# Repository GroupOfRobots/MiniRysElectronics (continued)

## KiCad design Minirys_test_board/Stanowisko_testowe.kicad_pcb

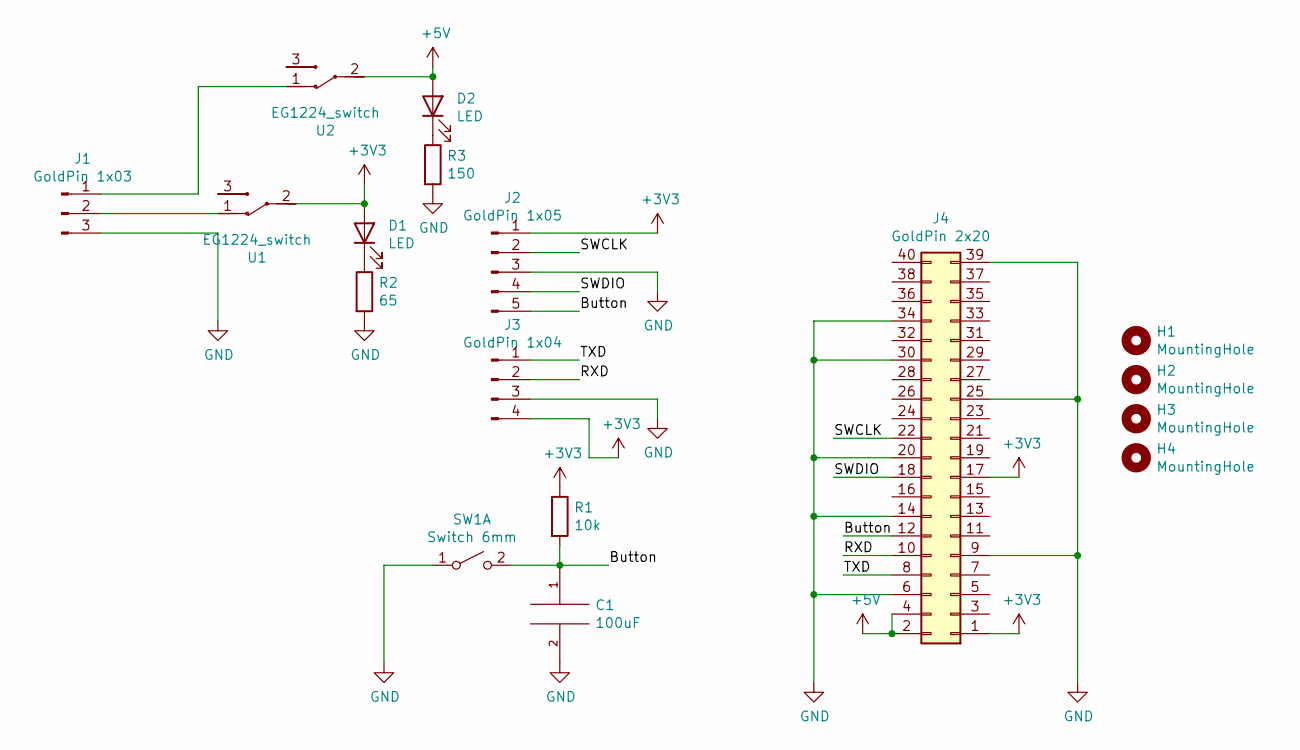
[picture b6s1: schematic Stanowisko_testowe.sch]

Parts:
C1: 100uF; C_0603_1608Metric_Pad1.08x0.95mm_HandSolder
D1, D2: LED; LED_0603_1608Metric
H1, H2, H3, H4: MountingHole; MountingHole_2.7mm_M2.5_Pad
J1: GoldPin 1x03; PinHeader_1x03_P2.54mm_Vertical
J2: GoldPin 1x05; PinHeader_1x05_P2.54mm_Vertical
J3: GoldPin 1x04; PinHeader_1x04_P2.54mm_Vertical
J4: GoldPin 2x20; PinHeader_2x20_P2.54mm_Vertical
R1: 10k; R_0603_1608Metric_Pad0.98x0.95mm_HandSolder
R2: 65; R_0603_1608Metric_Pad0.98x0.95mm_HandSolder
R3: 150; R_0603_1608Metric_Pad0.98x0.95mm_HandSolder
SW1: Switch 6mm; SW_PUSH_6mm
U1, U2: EG1224_switch; SW_E-Switch_EG1224_SPDT_Angled

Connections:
+3V3: D1.2 (A), J2.1, J3.4, J4.1, J4.17, R1.1, U1.2
+5V: D2.2 (A), J4.2, J4.4, U2.2
/Button: C1.1, J2.5, J4.12, R1.2, SW1.2 (B)
/RXD: J3.2, J4.10
/SWCLK: J2.2, J4.22
/SWDIO: J2.4, J4.18
/TXD: J3.1, J4.8
GND: C1.2, J1.3, J2.3, J3.3, J4.6, J4.9, J4.14, J4.20, J4.25, J4.30, J4.34, J4.39, R2.2, R3.2, SW1.1 (A)
unnamed: D1.1 (K), R2.1
unnamed: D2.1 (K), R3.1
unnamed: J1.1, U2.1
unnamed: J1.2, U1.1

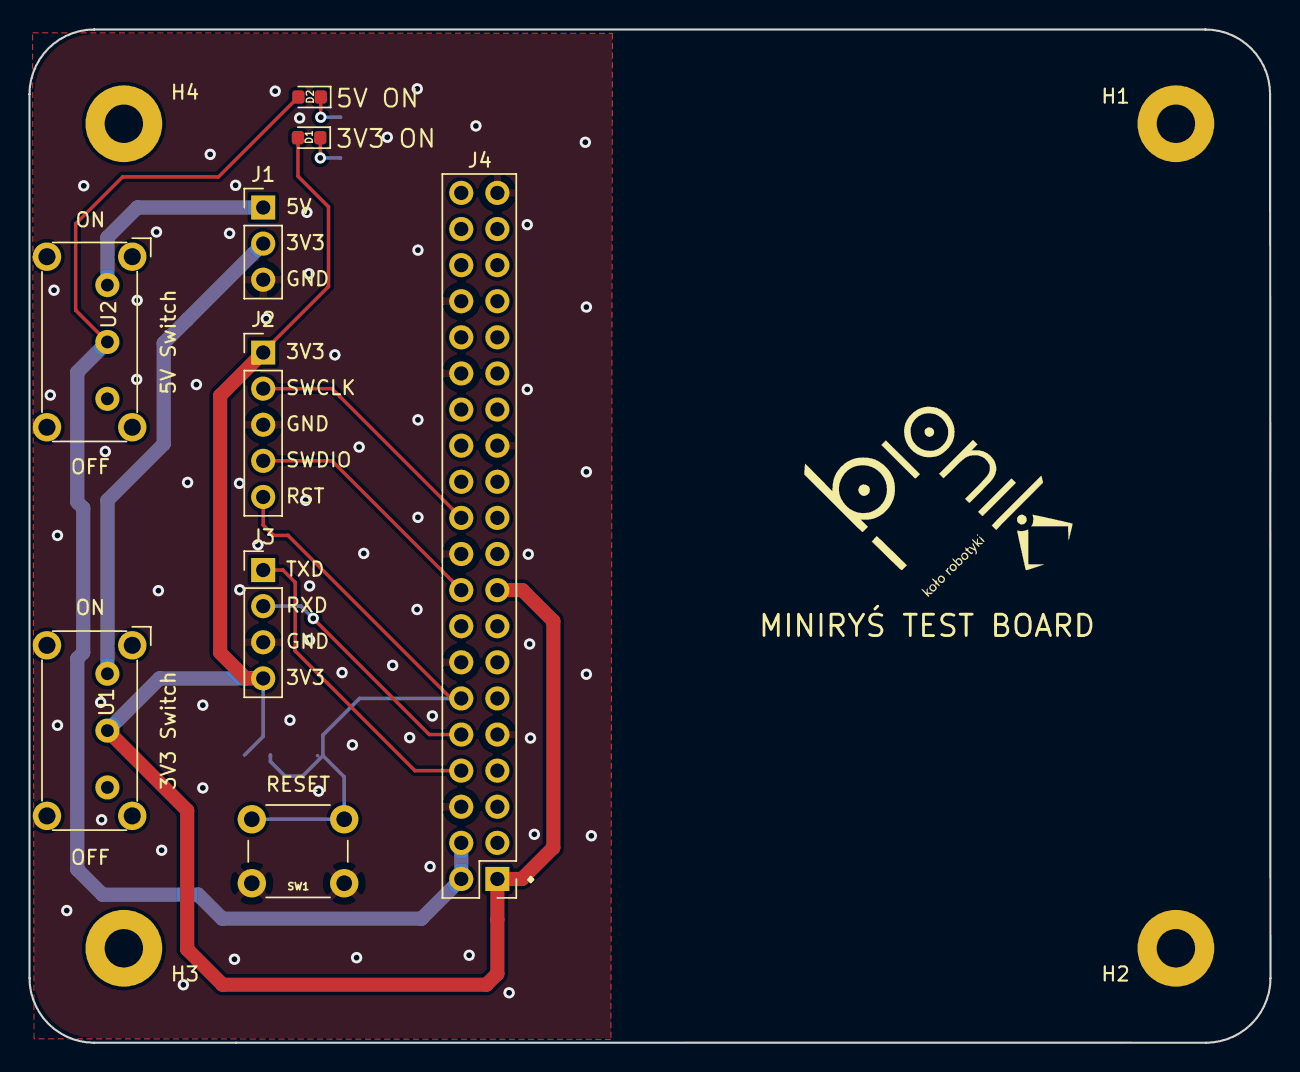
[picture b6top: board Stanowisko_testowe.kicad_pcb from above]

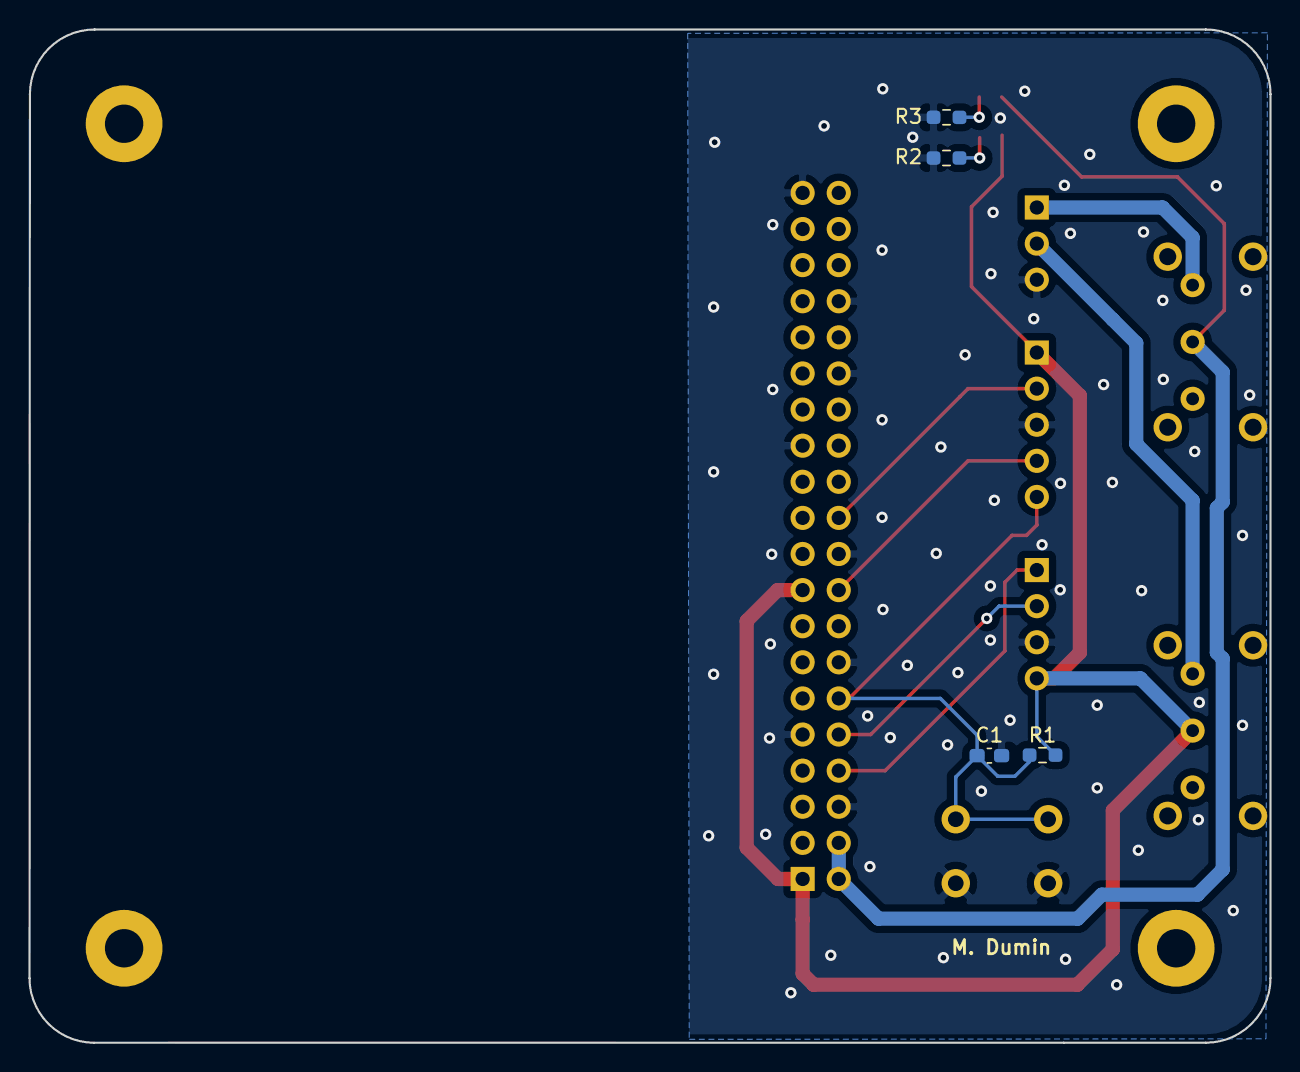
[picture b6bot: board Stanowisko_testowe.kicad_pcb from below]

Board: 2 copper layers, 87.3 x 71.3 mm, 18 parts (4 on the bottom side), 12 nets.

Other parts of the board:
LOGO1: bionik_logo

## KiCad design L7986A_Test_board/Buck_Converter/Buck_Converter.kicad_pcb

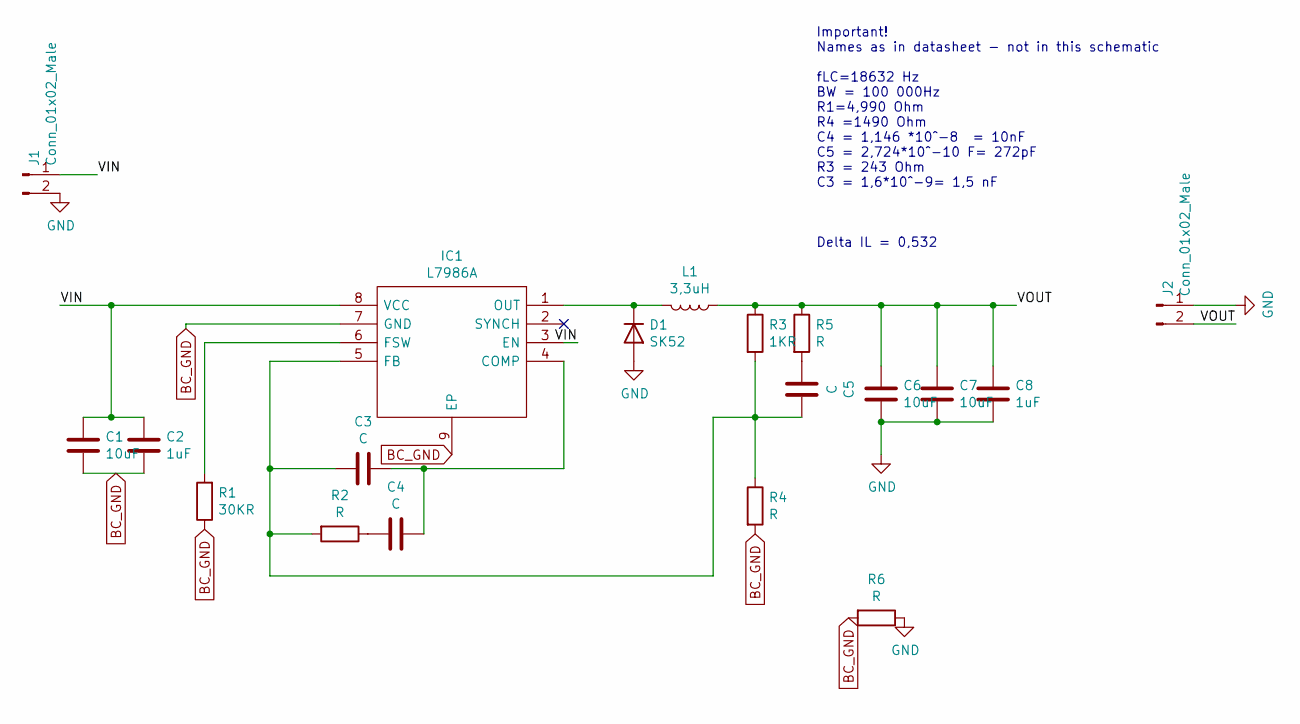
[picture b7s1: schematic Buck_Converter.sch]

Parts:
C1, C6, C7: 10uF; C_1206_3216Metric
C2: 1uF; C_0603_1608Metric
C3, C4, C5: C; C_0603_1608Metric
C8: 1uF; C_1206_3216Metric
D1: SK52; D_SMB
IC1: L7986A; SOIC127P600X170-9N; Mouser Part Number 511-L7986A
J1, J2: Conn_01x02_Male; PinHeader_1x02_P2.54mm_Vertical
L1: 3,3uH; L_6.3x6.3_H3
R1: 30KR; R_0603_1608Metric
R2, R4, R5, R6: R; R_0603_1608Metric
R3: 1KR; R_0603_1608Metric

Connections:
/VIN: C1.2, C2.2, IC1.3 (EN), IC1.8 (VCC), J1.1
/VOUT: C6.2, C7.2, C8.2, J2.2, L1.1, R3.1, R5.1
BC_GND: C1.1, C2.1, IC1.7 (GND), IC1.9 (EP), R1.1, R4.2, R6.2
GND: C6.1, C7.1, C8.1, D1.2 (A), J1.2, J2.1, R6.1
unnamed: C3.1, C4.1, IC1.4 (COMP)
unnamed: C3.2, C5.1, IC1.5 (FB), R2.2, R3.2, R4.1
unnamed: C4.2, R2.1
unnamed: C5.2, R5.2
unnamed: D1.1 (K), IC1.1 (OUT), L1.2
unnamed: IC1.6 (FSW), R1.2

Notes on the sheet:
Important! Names as in datasheet - not in this schematic fLC=18632 Hz BW = 100 000Hz R1=4,990 Ohm R4 =1490 Ohm C4 = 1,146 *10^-8 = 10nF C5 = 2,724*10^-10 F= 272pF R3 = 243 Ohm C3 = 1,6*10^-9= 1,5 nF Delta IL = 0,532

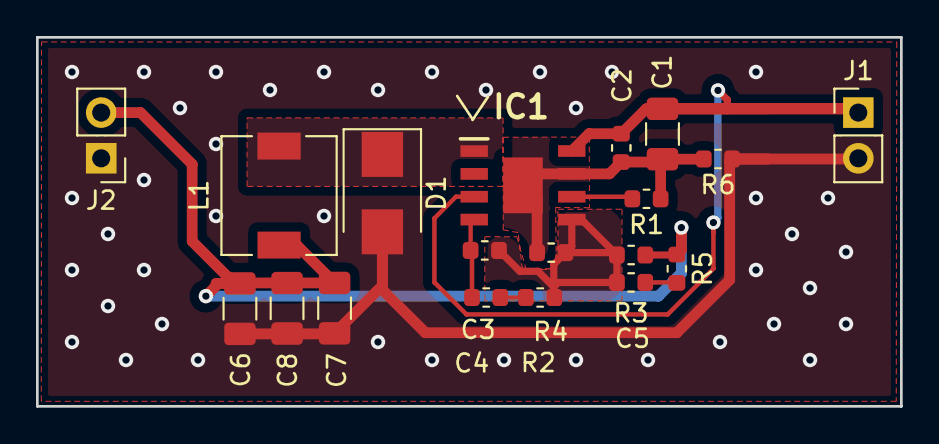
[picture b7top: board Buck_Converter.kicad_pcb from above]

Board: 2 copper layers, 48.0 x 20.5 mm, 19 parts (0 on the bottom side), 10 nets.

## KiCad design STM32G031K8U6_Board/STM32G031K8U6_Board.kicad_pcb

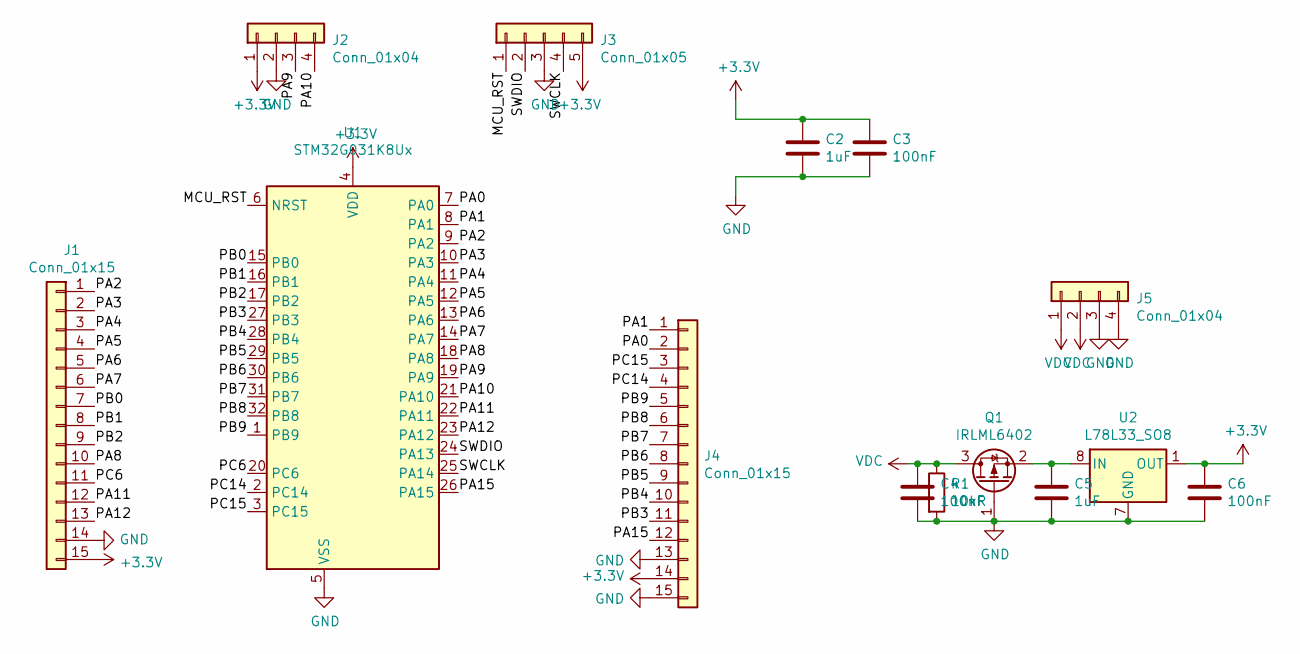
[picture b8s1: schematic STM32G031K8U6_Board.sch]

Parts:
C2, C5: 1uF; C_1206_3216Metric_Pad1.42x1.75mm_HandSolder
C3, C4, C6: 100nF; C_1206_3216Metric_Pad1.42x1.75mm_HandSolder
J1, J4: Conn_01x15; PinHeader_1x15_P2.54mm_Vertical
J2, J5: Conn_01x04; PinHeader_1x04_P2.54mm_Vertical
J3: Conn_01x05; PinHeader_1x05_P2.54mm_Vertical
Q1: IRLML6402; SOT-23
R1: 10kR; R_1206_3216Metric_Pad1.42x1.75mm_HandSolder
U1: STM32G031K8Ux; QFN-32-1EP_5x5mm_P0.5mm_EP3.45x3.45mm
U2: L78L33_SO8; SOIC-8_3.9x4.9mm_P1.27mm

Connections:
+3V3: C2.1, C3.1, C6.1, J1.15, J2.1, J3.5, J4.14, U1.4 (VDD), U2.1 (OUT)
/MCU_RST: J3.1, U1.6 (NRST)
/PA0: J4.2, U1.7 (PA0)
/PA1: J4.1, U1.8 (PA1)
/PA2: J1.1, U1.9 (PA2)
/PA3: J1.2, U1.10 (PA3)
/PA4: J1.3, U1.11 (PA4)
/PA5: J1.4, U1.12 (PA5)
/PA6: J1.5, U1.13 (PA6)
/PA7: J1.6, U1.14 (PA7)
/PA8: J1.10, U1.18 (PA8)
/PA9: J2.3, U1.19 (PA9)
/PA10: J2.4, U1.21 (PA10)
/PA11: J1.12, U1.22 (PA11)
/PA12: J1.13, U1.23 (PA12)
/PA15: J4.12, U1.26 (PA15)
/PB0: J1.7, U1.15 (PB0)
/PB1: J1.8, U1.16 (PB1)
/PB2: J1.9, U1.17 (PB2)
/PB3: J4.11, U1.27 (PB3)
/PB4: J4.10, U1.28 (PB4)
/PB5: J4.9, U1.29 (PB5)
/PB6: J4.8, U1.30 (PB6)
/PB7: J4.7, U1.31 (PB7)
/PB8: J4.6, U1.32 (PB8)
/PB9: J4.5, U1.1 (PB9)
/PC6: J1.11, U1.20 (PC6)
/PC14: J4.4, U1.2 (PC14)
/PC15: J4.3, U1.3 (PC15)
/SWCLK: J3.4, U1.25 (PA14)
/SWDIO: J3.2, U1.24 (PA13)
GND: C2.2, C3.2, C4.2, C5.2, C6.2, J1.14, J2.2, J3.3, J4.13, J4.15, J5.3, J5.4, Q1.1 (G), R1.2, U1.5 (VSS), U2.2 (GND), U2.3 (GND), U2.6 (GND), U2.7 (GND)
unnamed: C5.1, Q1.2 (S), U2.8 (IN)
VDC: C4.1, J5.1, J5.2, Q1.3 (D), R1.1

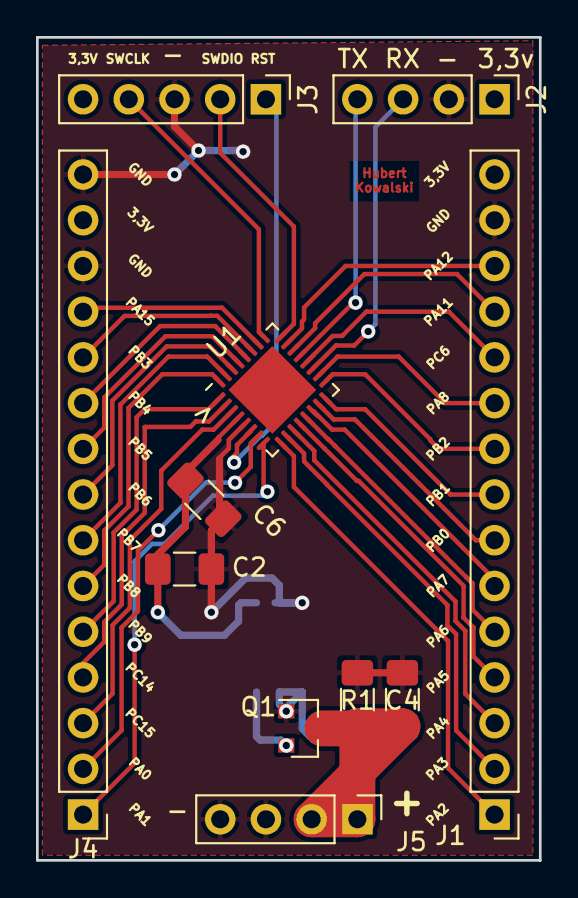
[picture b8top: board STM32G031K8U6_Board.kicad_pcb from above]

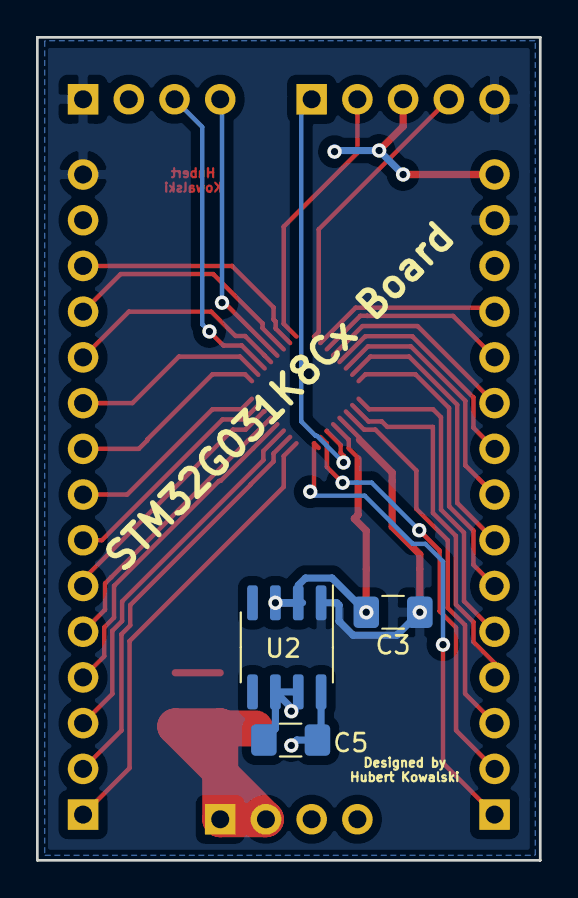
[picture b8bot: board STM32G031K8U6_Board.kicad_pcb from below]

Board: 2 copper layers, 27.9 x 45.7 mm, 14 parts (3 on the bottom side), 34 nets.

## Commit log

2016-03-23 initial
2016-03-28 nie chce misie
2016-03-31 initial board elements
2016-04-01 pcb updated
2016-04-01 allsmd
2016-04-05 allparts
2016-04-07 boardf
2016-04-07 clean
2016-05-11 useful mods
2016-06-19 starting new version
2016-06-19 beagleoutline
2016-06-21 powerconn
2016-06-25 powerconectors
2016-07-17 beaglepinout
2016-07-18 bgsignals
2016-07-18 schematiccomplete
2016-08-21 main wires
2016-08-24 boardv2 ready to check
2016-08-30 check pinout
2016-09-13 added distance sensor connectors
2016-09-26 gerbers
2016-10-09 gpioadjustment
2016-10-17 removes
2016-10-28 check and reconfigure gpios
2016-11-01 pin recinfiguration started
2016-11-06 new gpio routed started
2016-11-07 before logo
2016-11-07 v3gerbers
2016-11-13 pullups
2016-11-25 values
2016-12-11 right sonar wires
2017-01-26 new ideas
2017-04-06 v3init
2017-04-11 sdsd
2017-04-27 v3-ready
2017-04-30 ojojoj
2017-04-30 report
2017-05-05 gerbery
2017-05-06 wysłane
2017-06-16 TOF GPIO, pulldowns
2017-06-17 board 3.1: * zmienione szyny I2C1->I2C2, SPI1->SPI0 * poprawione dzielniki napięcia baterii * dodany dzielnik napięcia czujnika temperatury * poprawione etykiety i rozmieszczenie elementów na schemac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
2017-06-20 board v3.1 beta 5: przepięte 2 TOF i MEN,M0,M1,M2, usunięte rezystory z tych linii, rerouting
2017-06-21 gerber files, board report
2017-06-21 packed gerbers
2017-06-21 board v3.1 beta 6: poprawione dzielniki napięcia baterii na płytce
2017-06-23 board v3.1 beta 6: poprawiony minimalny rozmiar otworu (DRC)
2017-06-28 dwm1000_addon: mini-płytka na moduł dwm1000 wpinana na złącze goldpin
2017-07-07 dwm1000_addon: poprawione prowadzenie ścieżek masy
2017-07-07 board v3.1 beta 6: poprawione acid-trap przy dzielnikach napięcia baterii
2017-07-07 board v3.1 beta 7: replaced DWM1000 module with connector for dwm1000-addon board, redone battery cell voltage routes. No more vias.
2017-07-07 board v3.1 beta 7: fixed bad networks between motor drivers and connectors; fixed some clearance issues
2017-07-07 beacon: import płytki latarni lokalizacyjnej z repo RobotLocalization; rev 1.1: dwm1000 zastąpiony złączem na dwm1000-addon
2017-07-20 dwm1000_addon: zmniejszone pole masy pod anteną, przesunięte diody aktywności
2017-07-31 gitignore: gerbery dodane do ignorowanych
2017-07-31 latarnia (beacon): zmniejszone wymiary płytki
2017-07-31 dwm1000 addon: dodane pola masy
2017-08-01 dodane wymiary zewnętrzne płytek
2017-08-01 dodane archiwa z przygotowanymi gerberami aktualnych wersji płytek
2017-12-13 board3.1: updated resistors on voltage divider for power
2018-03-03 v4 init
2018-07-19 battery pcb model
2018-08-07 pico blade connectors
2018-10-17 raspberry layout
2018-10-18 power button
2018-10-21 battery module
2018-10-25 new battery module
2018-10-25 revision
2018-11-28 v4.1 schematic
2018-11-29 board adjustments on PCB
2018-12-04 v4.1
2018-12-27 regulator devider
2019-03-02 clean up repo and add TODO task
2019-03-02 improved battery module pads
2019-03-17 voltage devider fix
2019-04-13 ADC voltage divider
2019-05-18 v 4.1
2019-06-08 closed version 4.1
2019-08-05 new pads
2020-03-22 remove old versions (existing in git history)
2020-03-29 rysboard: converted to kicad (initial version)
2020-03-29 rysboard: rpi4 connector and power supply cleaned up after import; clean up library and gitignore file
2020-03-29 rysboard: schematic cleanup done after kicad import
2020-03-29 rysboard: library cleanup, fix bad connector references
2020-04-19 rysboard: 4.2 schematic
    Change the I2C buses and GPIOs used
    Fix L6470 connections
    Change ADC to 4-channel
    Add 2 user LEDs
    Add I2C pullups
    Add serial connector
2020-04-19 rysboard: 4.2 schematic imported to pcb, initial version
2020-05-16 rysboard 4.2: * add converter output protection (shottky, D8) * fix converter resistor values (R13/R14) * add 5Vgood LED (D9) * add PWR_FLAGs for KiCAD's ERC * add NAND for motor driver's output flag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
2020-05-16 rysboard v4.2: * route the whole board (TODO: ground fills, track width checks) * fix half of ToF connectors missing ground connection * swap LEDs for easier routing
2020-05-16 rysboard v4.2: adjust placement of text on pcb front side silkscreen
2020-05-17 rysboard v4.2: * re-add mountting holes * fix some layout errors * add ground fills * ensure proper track width * add front-side filkscreen
2020-05-17 rysboard v4.2: adjust silkscreen text positions, add board name, minor layout improvements
2020-05-19 rysboard v4.2: custom 6.7x6.7mm inductor footprint&model
2020-05-19 rysboard v4.2: status LED transistor swapped for BC847BS; PCB design fixes after review (!1)
2020-05-20 rysboard: remove additional i2c pullups; increase high-voltage track clearance
2020-05-24 rysboard: changed LED and sensors' VCC to 5V
2020-05-26 rysboard: move spi external interrupt line further from the edge
2020-06-24 rysboard: fix pour between SMD pins, fix acid pits, add +/- labels to battery connectors and Vdrive test point/area
2020-06-27 rysboard: fix additional acid pits, C15 cap placement, text orientation, added BIONIK logo and external SPI connector pinout
2020-06-27 rysboard: add missing molex 3d models
2020-08-23 rysboard: add PWM fan output
2020-10-23 rysboard: move the camera ribbon slot closer to the port on the Pi
2020-10-23 rysboard: fix leftover acid pits
2020-11-12 rysboard: move D8 before converter feedback; replace U5 with counterpart of higher availability; fix U4 wiring; improve GND connections to motor drivers
2020-11-21 rysboard: add missing BIONIK logo on silkscreen front
2020-12-12 rysboard: add BIONIK logo to schematic (to prevent it disappearing from PCB after every update)
2021-01-01 added Battery Baalancing, Reverse polarity protection circuits and skeleton of power managment
2021-01-14 rysboard: fix BIONIK logo, fix ADC footprint, final version (sent to mfg)
2021-02-22 Added mcu, labeled its pins , major powwer supply overhaul started
2021-02-22 readme updated
2021-02-22 DMP3036SSD footprint added
2021-02-22 NST847BDP6T5G Added, more conections done
2021-02-23 created eval board for STM , added mcu, created controll section for TOFS and FAN. Added programming pinout, Remooved legacy spi interface, Removed addidtional i2c socket
2021-02-24 added some of the analog sensors
2021-02-25 cleanup
2021-02-26 first modyfications in St Motor section
2021-02-26 Added eval board for STM32G031K8U6, rybsoard layout done, exact vals yet to be calculated
2021-02-27 sensors enable added, Vref problem to solve
2021-03-03 new mosfet footprints
2021-03-04 Fixed library, added a few MOSFET layouts
2021-03-04 battery Balancing specified
2021-03-05 more work done
2021-03-06 more footprints
2021-03-08 ltc4007 configured
2021-03-11 LTC4007 done
2021-03-12 Even More footprints
2021-03-16 More Work. RPI can now programm STM32 via GPIO
2021-03-19 pre cleanup
2021-03-20 cleanup and energy managment scheeme started
2021-03-22 started board project
2021-03-23 fixed some bugs. Input protection done. Started implementing 5V Regulator
2021-03-24 step down implemented
2021-03-25 st motor drivers done
2021-03-26 3,3Vreg added. MCU first placement
2021-03-27 stm scheeme
2021-03-29 mcu IO
2021-04-03 MCU Sensors Done
2021-04-10 rysbattery: kicad version
2021-04-12 first version
2021-04-16 rysbattery: remove old version (remains in git history)
2021-04-25 layout finished - no error checks
2021-04-30 version pre changes due to scarsity of parts
2021-05-02 Bom finished pcb cleanup started
2021-05-03 bom + excel ready
2021-05-07 Step down L7986A test board
2021-05-07 Board zones added
2021-05-07 changed ST1S10 Footprint to old one
2021-05-07 removed ST1S10
2021-05-07 cleanup done
2021-05-07 bat protection done
2021-05-08 vin protection added
2021-05-09 New Layout done TODo Error Check
2021-05-10 Filled zones fixed
2021-05-11 Labels Fixed
2021-05-13 pre stiching
2021-05-13 layers stiched
2021-05-19 Fixed regulator footprint
2021-05-23 added connector for switch
2021-05-24 Bionik Logo added
2021-06-07 some acid pits fixed some ground problems fixed
2021-09-11 test board
2021-09-11 porządki
2021-09-11 porzadki 2
2023-06-20 transfer from my msc repo
2023-11-15 Uploaded all project files
2023-11-15 Added README.md
2023-11-16 Added project files (KiCad project)
2023-11-23 Added required connectors for this version
    Also did some file name changes
2023-12-07 Finished motor drivers schematic
    Still need to connect all the connectors and sort out old unused connections
2023-12-13 New complete schematic version
    May need to resize the resistors, also need to change the caps back to electrolytic
2024-03-25 Uploaded all project files, finished PCB design
2024-10-03 Trace routing corrections, prepared for further modifications
2024-10-03 Fixed outdated connector footprints
2024-10-03 Adjusted south connectors position
2024-10-03 Minimized empty space in copper pour
2024-10-03 Fixed reference designators positioning
2024-10-03 Added 3V0 net for L6470H's internal voltage regulator and updated schematic with stabilization caps
2024-10-08 Left drivers internal voltage regulator now has its own capacitors
2024-10-09 Separated 3V0 and 3V3 lines, right motor driver properly connected, fixed trace pathing
2024-10-09 Added proper silkscreen info for connectors
2024-10-10 Changed fan connector type to THT
2024-10-10 Added useful markings on silkscreen
